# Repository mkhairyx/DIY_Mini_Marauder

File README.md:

# DIY_Mini_Marauder

This is an open source version of [JustCallMeKoko's](github.com/justcallmekoko) marauder mini with better documentation and tutorials on how flash the device after making it. <br>
<br>

The reason I made this repository is becaused I have always wanted to have my own marauder mini but it was unavailble and there was no Schematics to be found for it. <br>
Only thing I was able to find was the PCB and the Case for it. I reverse engineered the PCB to have a useful schematic that anyone can use to make their own PCB and maybe make changes to it. <br>

## The Poster

## The Design
### The PCB

### The Schematics

### The Enclosure Case 
With the device inside:

Without the device inside:

## Assembly
### Step Files
All of the step files can be downloaded [here](./Step_Files/).

### Disassembly video

https://github.com/user-attachments/assets/7e853b93-fa27-431c-8479-e6c7b8179391

## Firmware
### Fzee flasher (Marauder Mini)
- Visit the [FZEE FLASHER](https://fzeeflasher.com/) website
- Make sure your device is connected to your PC
- Click "Connect" <br>

- Select the Programmer chip for your device (which would be CP2104 if you used the schematics/PCB in this repository) <br>

- If you used the schematics/PCB provided in this repository, then you can skip this step. <br>
As soon as you see this screen, hold down the BOOT button on your device as the flasher will automatically reset the device and it will go into the boatloader mode <br>

- Select "ESP32 Marauder Mini Device" <br>

- Select the latest version <br>

- Select "Marauder" as the firmware <br>

- Erase the device first to make sure that it's not affected by any previously installed firmwares <br>

- Click "Program" <br>

- It will take arround 10 seconds to flash the firmware.  <br>
  After those 10 seconds, you should see this screen which indicates that you succesfully flashed the device with the new firmware: <br>

### Bruce (Bruce's Firmware)
- Visit [Bruce's Web Firmware Flasher](https://bruce.computer/flasher) 
- Select whatever release you want (it's recommended to select the latest release)

- Select "Custom Boards"

- Select "Marauder Mini"

- Select "Connect to Device"

- Select the Programmer chip for your device (which would be CP2104 if you used the schematics/PCB in this repository)

- Select "Instal Marauder-Mini"

- Then make sure to have the "Erase device" option enabled then click next

- Confirm the instalation

- If you used the schematics/PCB provided in this repository, then you can skip this step. <br>
As soon as you see this screen, make sure to put your device into the bootloader mode by holding the BOOT button down, pressing the RST button, and then after 2 seconds release the BOOT button.

- It will take around 2 minutes to upload the firmware. <br>
After those 2 minutes, you should see this screen which indicates that you had a succesful instalation:

## Buttons and leds
### The two LEDs
Next to the USB-C port there are 2 LEDs: <br>
- The white one indicates wether the device is powered or not. <br>
- The blue one indicates wether the device is recieved power from the USB-C port or not (which is used to charge the battery).

### The two buttons on the back of the device and their functions
- The Upper button is used to put the ESP32 into the bootloader mode (AKA. the BOOT button). <br>
- The lower button is used to reset the device (AKA. the RST button).<br>

### The side switch
- The side switch is used to power the device ON or OFF.

## BOM
### BOM table (components only)
|Name                            |Value                       |Link                                                                                                                                                                                                                                                                                                                                                                    |Cost (EGP) per one|Cost (USD)|Total Cost (EGP)                           |Total Cost (USD)|Qty of packages|Description          |quantiy per pack|
|--------------------------------|----------------------------|------------------------------------------------------------------------------------------------------------------------------------------------------------------------------------------------------------------------------------------------------------------------------------------------------------------------------------------------------------------------|------------------|----------|-------------------------------------------|----------------|---------------|---------------------|----------------|
|Capacitor                       |100nF                       |https://lampatronics.com/product/smd-multilayer-ceramic-capacitor-0805-2012-104-100nf-50v-1pcs-2                                                                                                                                                                                                                                                                        | EGP 1.00         | $0.02    | EGP 3.00                                  | $0.06          |3              |                     |1               |
|Capacitor                       |4.7uF                       |https://lampatronics.com/product/smd-multilayer-ceramic-capacitor-1206-4-7uf-16v-1pcs                                                                                                                                                                                                                                                                                   | EGP 1.50         | $0.03    | EGP 4.50                                  | $0.09          |3              |                     |1               |
|Capacitor                       |2.2uF                       |https://lampatronics.com/product/smd-multilayer-ceramic-capacitor-0805-2-2uf-50v-1pcs                                                                                                                                                                                                                                                                                   | EGP 1.00         | $0.02    | EGP 1.00                                  | $0.02          |1              |                     |1               |
|SD Card slot                    |TF-115                      |https://lampatronics.com/product/push-push-type-tf-micro-sd-card-socket-adapter-automatic-pcb-connector                                                                                                                                                                                                                                                                 | EGP 8.00         | $0.15    | EGP 8.00                                  | $0.15          |1              |                     |1               |
|Charging LED                    |SZYY0603Y                   |https://lampatronics.com/product/smd-led-0805-blue-10pcs                                                                                                                                                                                                                                                                                                                | EGP 8.00         | $0.15    | EGP 8.00                                  | $0.15          |1              |Charge LED (RED)     |10              |
|Power LED                       |SZYY0603Y                   |https://lampatronics.com/product/smd-led-0805-white-10pcs                                                                                                                                                                                                                                                                                                               | EGP 8.00         | $0.15    | EGP 8.00                                  | $0.15          |1              |Power LED (White)    |10              |
|Schottky Diode                  |MBR120LSF (alt: 1N5819 SS14)|https://uge-one.com/product/smd-schottky-diode-1n5819-ss14-1a-40v-sma-package/                                                                                                                                                                                                                                                                                          | EGP 2.50         | $0.05    | EGP 2.50                                  | $0.05          |1              |Schottky             |1               |
|JST Connector                   |S2B-PH-SM4-TB               |https://uge-one.com/product/jst-connector-male-polarized-xh2-54-2p/                                                                                                                                                                                                                                                                                                     | EGP 1.14         | $0.02    | EGP 1.14                                  | $0.02          |1              |JST connector        |1               |
|BOOT and RESET transistors      |S8050                       |https://lampatronics.com/product/s8050-transistor-40v-0-5a-npn                                                                                                                                                                                                                                                                                                          | EGP 0.50         | $0.01    | EGP 1.00                                  | $0.02          |2              |RST&BOOT transistors |1               |
|Power management and TFT LED PWM|AO3401                      |https://uge-one.com/product/ao3401-sot23-general-purpose-p-channel-mosfet-smd-transistor-sot-23/                                                                                                                                                                                                                                                                        | EGP 3.00         | $0.06    | EGP 6.00                                  | $0.12          |2              |Power manage, TFT LED|1               |
|Resistor                        |5.1k                        |https://uge-one.com/product/smd-chip-resistor-size-0603-5-1k-ohm/                                                                                                                                                                                                                                                                                                       | EGP 0.50         | $0.01    | EGP 1.00                                  | $0.02          |2              |USB-C resistors 5.1k |1               |
|Resistor                        |10K                         |https://lampatronics.com/product/smd-resistor-10kohm-103-0805-10pcs                                                                                                                                                                                                                                                                                                     | EGP 2.00         | $0.04    | EGP 4.00                                  | $0.08          |2              |                     |10              |
|Resistor                        |1K                          |https://lampatronics.com/product/smd-resistor-1kohm-102-0805-10pcs                                                                                                                                                                                                                                                                                                      | EGP 2.00         | $0.04    | EGP 2.00                                  | $0.04          |1              |                     |10              |
|Prog Resistor                   |2K                          |https://lampatronics.com/product/smd-resistor-2kohm-202-0805-10pcs                                                                                                                                                                                                                                                                                                      | EGP 2.00         | $0.04    | EGP 2.00                                  | $0.04          |1              |                     |10              |
|RST and BOOT buttons            |SW_Omron_B3FS               |https://lampatronics.com/product/smd-push-button-3425mm-tactile-tact-micro-switch-momentary-4pin                                                                                                                                                                                                                                                                        | EGP 3.00         | $0.06    | EGP 6.00                                  | $0.12          |2              |                     |1               |
|LDO Enable Switch               |K3-1296S-E1_C128955         |https://uge-one.com/product/horizontal-small-slide-toggle-switch-spdt-3pin-2mm-pin-spacing-sk12d02vg7/                                                                                                                                                                                                                                                                  | EGP 4.00         | $0.08    | EGP 4.00                                  | $0.08          |1              |Power slide switch   |1               |
|directional buttons             |                            |https://lampatronics.com/product/push-button-4pin-long-6x6x13mm                                                                                                                                                                                                                                                                                                         | EGP 1.50         | $0.03    | EGP 7.50                                  | $0.14          |5              |Directional switch   |1               |
|MCU                             |ESP32-WROOM-32              |https://uge-one.com/product/espressif-esp32-wroom-32-dual-core-wi-fi-bluetooth-iot-module/                                                                                                                                                                                                                                                                              | EGP 290.00       | $5.58    | EGP 290.00                                | $5.58          |1              |MCU                  |1               |
|Battery charger                 |MCP73831T-2ACI_OT           |[Long Aliexpress link](https://ar.aliexpress.com/item/32844180448.html?spm=a2g0o.productlist.main.1.3ce63cd6piQzMy&algo_pvid=c4aa9c81-0eb9-4713-ae7a-3ae3d38d7e01&pdp_ext_f=%7B%22order%22%3A%22167%22%2C%22spu_best_type%22%3A%22price%22%2C%22eval%22%3A%221%22%2C%22fromPage%22%3A%22search%22%7D&utparam-url=scene%3Asearch%7Cquery_from%3A%7Cx_object_id%3A32844180448%7C_p_origin_prod%3A)| N/A              | $4.28    | N/A                                       | $4.28          |1              |Battery Charger      |10              |
|Programmer                      |CP2104                      |[Long Aliexpress link](https://ar.aliexpress.com/item/1005012309258723.html?pdp_ext_f=%7B%22sku_id%22%3A%2212000058021215527%22%7D&sourceType=1&spm=a2g0o.wish-manage-home.0.0&gatewayAdapt=glo2ara)                                                                                                                                                                    | N/A              | $1.97    | N/A                                       | $1.97          |1              |USB to TTL chip      |1               |
|LDO Regulator                   |MIC5219-3.3YM5              |[Long Aliexpress link](https://ar.aliexpress.com/item/1005006130724980.html?spm=a2g0o.productlist.main.6.4c73EOI6EOI6w7&algo_pvid=ba305fa5-d1fa-45ea-b339-9e0b52087c6d&pdp_ext_f=%7B%22order%22%3A%2222%22%2C%22eval%22%3A%221%22%2C%22fromPage%22%3A%22search%22%7D&utparam-url=scene%3Asearch%7Cquery_from%3A%7Cx_object_id%3A1005006130724980%7C_p_origin_prod%3A)   | N/A              | $4.23    | N/A                                       | $4.23          |1              |LDO regulator        |10              |
|Display                         |TFT_1.44                    |[Long Aliexpress link](https://ar.aliexpress.com/item/1005001598020071.html?spm=a2g0o.order_list.order_list_main.5.714d1802IvCG36&gatewayAdapt=glo2ara)                                                                                                                                                                                                                 | N/A              | $2.16    | N/A                                       | $2.16          |1              |                     |1               |
|USB-C                           |USB_C_Receptacle_USB2.0_16P |https://www.ram-e-shop.com/shop/usb9-c-type-pcb-usb-connector-on-pcb-c-type-type-female-16-pin-sku-usb9-8125                                                                                                                                                                                                                                                            | EGP 5.00         | $0.10    | EGP 5.00                                  | $0.10          |1              |                     |1               |
|Battery                         |700 mah                     |https://lampatronics.com/product/battery-polymer-3-7v-700mah-li-ion-single-cell-35x20x5mm-502035                                                                                                                                                                                                                                                                        | EGP 135.00       | $2.60    | EGP 135.00                                | $2.60          |1              |                     |1               |
|M5 Screws                       |M5*16mm                     |https://store.fut-electronics.com/products/screw-m5x16mm-hexagonal-head?_pos=15&_sid=376b1bf88&_ss=r                                                                                                                                                                                                                                                                    | EGP 2.00         | $0.04    | EGP 2.00                                  | $0.04          |1              |                     |1               |
|                                |                            |                                                                                                                                                                                                                                                                                                                                                                        |                  |          |                                           |                |               |                     |                |
|                                |                            |                                                                                                                                                                                                                                                                                                                                                                        |                  |          | EGP 501.64                                | $22.29         |               |                     |                |
|                                |                            |                                                                                                                                                                                                                                                                                                                                                                        |                  |          | (Stuff from aliexpress not included here) |                |               |                     |                |

### Orders from different manufacturers
#### In Egypt
[Nori](norisolutions.com) (PCB only): $19.09 <br>

<br>

 [Metanoia](metanoia-eg.com) (Case only): $5.96 <br>
 
<br>

#### Out of Egypt
[JLCPCB](https://jlcpcb.com/) (both PCB and Case): $31.15 <br>

<br>
<br>
<br>

<h1 align="center"> DISCLAIMER </h1>

<h4 align="center">Please note that the use of this tool is entirely at your own risk. It is intended strictly for educational purposes and should not be used for any illegal or unethical activities. Jamming is illegal and can get you in big trouble!</h4>
<h4 align="center">I'm not responsible for your actions! </h4>

<br>

> The firmware is designed by [JustCallMeKoko](github.com/justcallmekoko). <br>
The PCB that was reverse engineered for the making of [DIY Mini Marauder](https://github.com/mkhairyx/DIY_Mini_Marauder) is designed by [JustCallMeKoko](https://github.com/justcallmekoko).<br>
This repo and all of it's contents were Designed by [@mkhairyx](https://github.com/mkhairyx).<br>
Supported by [Fallout](https://fallout.hackclub.com/) and [Hack Club](https://hackclub.com).<br>

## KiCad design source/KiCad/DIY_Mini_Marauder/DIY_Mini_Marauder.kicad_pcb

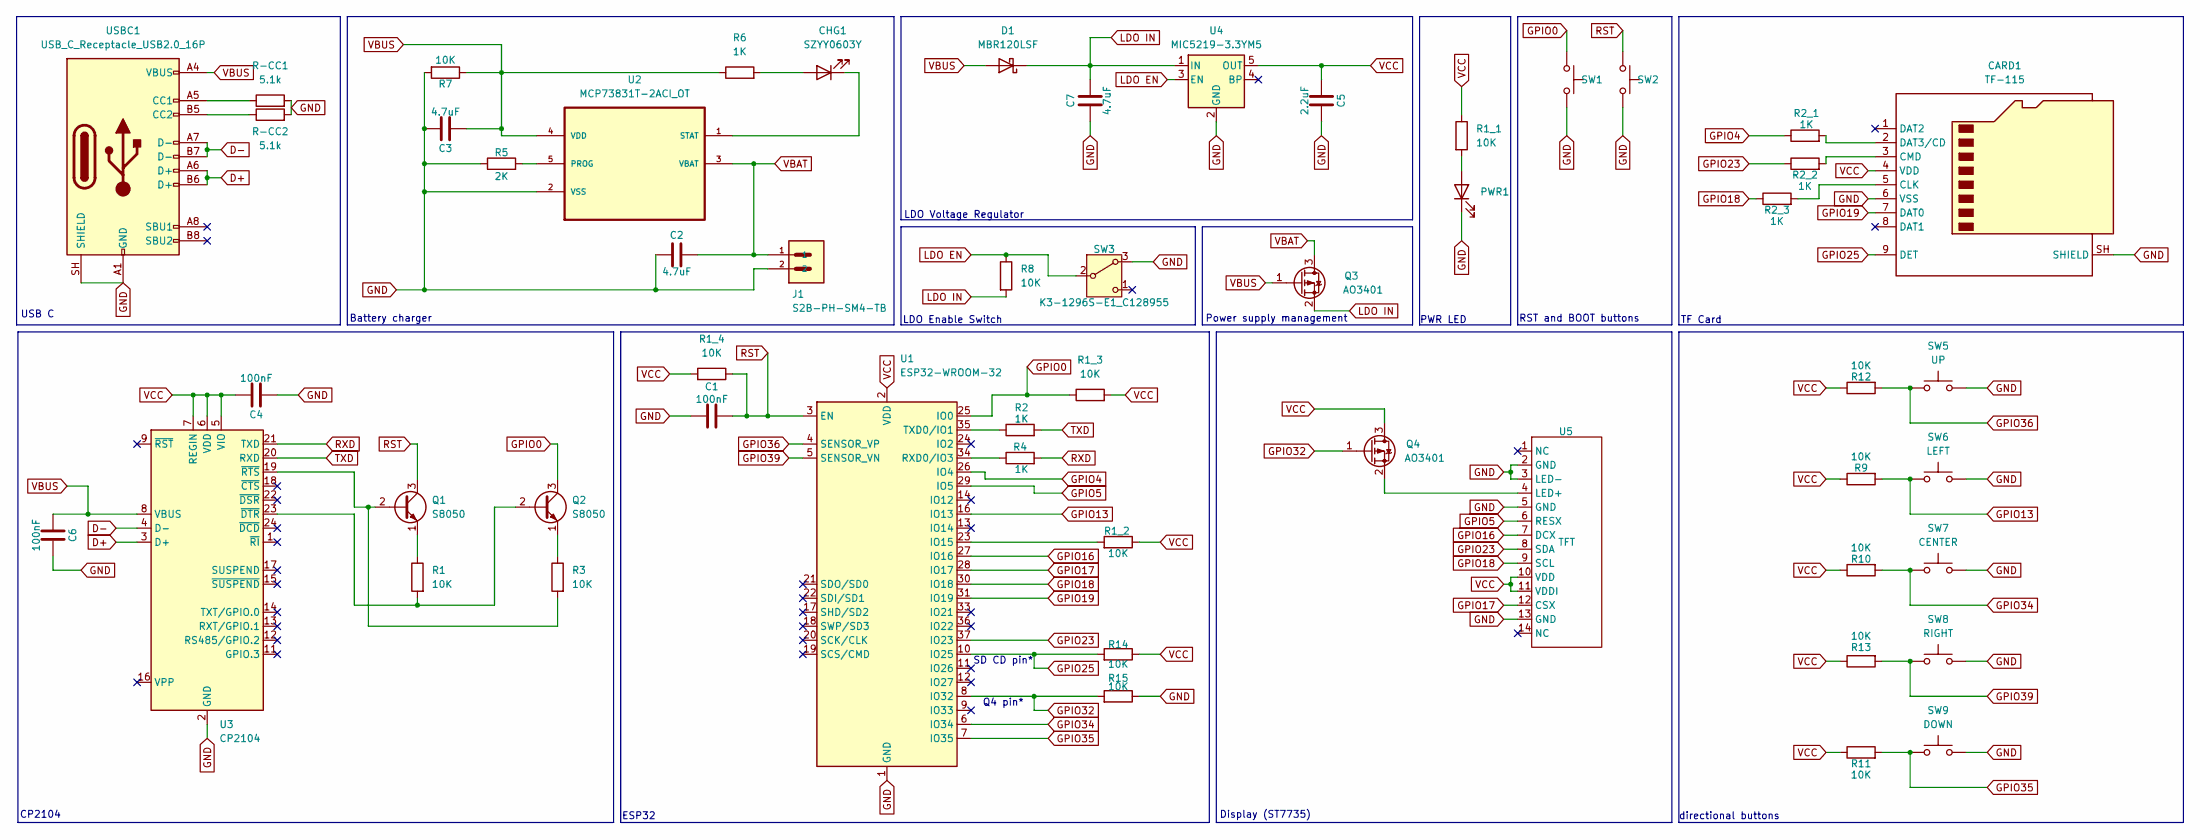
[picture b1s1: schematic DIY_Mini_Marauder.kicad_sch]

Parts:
C1, C4, C6: 100nF; C_0805_2012Metric_Pad1.18x1.45mm_HandSolder
C2, C3, C7: 4.7uF; C_1206_3216Metric_Pad1.33x1.80mm_HandSolder
C5: 2.2uF; C_0805_2012Metric_Pad1.18x1.45mm_HandSolder
CARD1: TF-115
CHG1: SZYY0603Y; LED_0805_2012Metric_Pad1.15x1.40mm_HandSolder
D1: MBR120LSF; D_SMA_Handsoldering
J1: S2B-PH-SM4-TB; JST_EH_B2B-EH-A_1x02_P2.50mm_Vertical
PWR1: SZYY0603Y; LED_0805_2012Metric_Pad1.15x1.40mm_HandSolder
Q1, Q2: S8050; TO-92
Q3, Q4: AO3401; SOT-23
R1, R1_1, R1_2, R1_3, R1_4, R3, R7, R8, R9, R10, R11, R12, R13, R14, R15: 10K; R_0805_2012Metric_Pad1.20x1.40mm_HandSolder
R2, R2_1, R2_2, R2_3, R4, R6: 1K; R_0805_2012Metric_Pad1.20x1.40mm_HandSolder
R5: 2K; R_0805_2012Metric_Pad1.20x1.40mm_HandSolder
R-CC1, R-CC2: 5.1k; R_0603_1608Metric_Pad0.98x0.95mm_HandSolder
SW1, SW2: SW_Omron_B3FS; SW_SPST_PTS810
SW3: K3-1296S-E1_C128955; SW_Slide_SPDT_Angled_CK_OS102011MA1Q
SW5: UP; SW_PUSH_6mm_H13mm
SW6: LEFT; SW_PUSH_6mm_H13mm
SW7: CENTER; SW_PUSH_6mm_H13mm
SW8: RIGHT; SW_PUSH_6mm_H13mm
SW9: DOWN; SW_PUSH_6mm_H13mm
U1: ESP32-WROOM-32
U2: MCP73831T-2ACI_OT; SOT-23-5_HandSoldering; MPN MCP73831T-2ACI/OT
U3: CP2104; QFN-24-1EP_4x4mm_P0.5mm_EP2.6x2.6mm
U4: MIC5219-3.3YM5; SOT-23-5_HandSoldering
U5: TFT; ST7735_TFT_14P
USBC1: USB_C_Receptacle_USB2.0_16P; USB_C_Receptacle_GCT_USB4105-xx-A_16P_TopMnt_Horizontal

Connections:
D+: U3.3 (D+), USBC1.A6 (D+), USBC1.B6 (D+)
D-: U3.4 (D-), USBC1.A7 (D-), USBC1.B7 (D-)
GND: C1.1, C2.1, C3.2, C4.1, C5.2, C6.2, C7.1, CARD1.6 (VSS), CARD1.SH (SHIELD), J1.2, PWR1.1 (K), R5.1, R7.2, R15.1, R-CC1.2, R-CC2.2, SW1.1, SW2.1, SW3.3 (A), SW5.2, SW6.2, SW7.2, SW8.2, SW9.2, U1.1 (GND), U1.15 (GND), U1.38 (GND), U1.39 (GND), U2.2 (VSS), U3.2 (GND), U3.25 (GND), U4.2 (GND), U5.2 (GND), U5.3 (LED-), U5.5 (GND), U5.13 (GND), USBC1.A1 (GND), USBC1.A12 (GND), USBC1.B1 (GND), USBC1.B12 (GND), USBC1.SH (SHIELD)
GPIO0: Q2.3 (C), R1_3.1, SW1.2, U1.25 (IO0)
GPIO4: R2_1.1, U1.26 (IO4)
GPIO5: U1.29 (IO5), U5.6 (RESX)
GPIO13: R9.2, SW6.1, U1.16 (IO13)
GPIO16: U1.27 (IO16), U5.7 (DCX)
GPIO17: U1.28 (IO17), U5.12 (CSX)
GPIO18: R2_3.1, U1.30 (IO18), U5.9 (SCL)
GPIO19: CARD1.7 (DAT0), U1.31 (IO19)
GPIO23: R2_2.1, U1.37 (IO23), U5.8 (SDA)
GPIO25: CARD1.9 (DET), R14.2, U1.10 (IO25)
GPIO32: Q4.1 (G), R15.2, U1.8 (IO32)
GPIO34: R10.2, SW7.1, U1.6 (IO34)
GPIO35: R11.2, SW9.1, U1.7 (IO35)
GPIO36: R12.2, SW5.1, U1.4 (SENSOR_VP)
GPIO39: R13.2, SW8.1, U1.5 (SENSOR_VN)
LDO EN: R8.1, SW3.2 (B), U4.3 (EN)
LDO IN: C7.2, D1.1 (K), Q3.2 (S), R8.2, U4.1 (IN)
unnamed: CARD1.5 (CLK), R2_3.2
unnamed: CARD1.3 (CMD), R2_2.2
unnamed: CARD1.2 (DAT3/CD), R2_1.2
unnamed: CHG1.2 (A), R6.2
unnamed: CHG1.1 (K), U2.1 (STAT)
unnamed: PWR1.2 (A), R1_1.2
unnamed: Q1.2 (B), R3.2, U3.19 (~RTS)
unnamed: Q1.1 (E), R1.1
unnamed: Q2.2 (B), R1.2, U3.23 (~DTR)
unnamed: Q2.1 (E), R3.1
unnamed: Q4.2 (S), U5.4 (LED+)
unnamed: R1_2.2, U1.23 (IO15)
unnamed: R4.1, U1.34 (RXD0/IO3)
unnamed: R2.1, U1.35 (TXD0/IO1)
unnamed: R5.2, U2.5 (PROG)
unnamed: R-CC1.1, USBC1.A5 (CC1)
unnamed: R-CC2.1, USBC1.B5 (CC2)
RST: C1.2, Q1.3 (C), R1_4.1, SW2.2, U1.3 (EN)
RXD: R4.2, U3.21 (TXD)
TXD: R2.2, U3.20 (RXD)
VBAT: C2.2, J1.1, Q3.3 (D), U2.3 (VBAT)
VBUS: C3.1, C6.1, D1.2 (A), Q3.1 (G), R6.1, R7.1, U2.4 (VDD), U3.8 (VBUS), USBC1.A4 (VBUS), USBC1.A9 (VBUS), USBC1.B4 (VBUS), USBC1.B9 (VBUS)
VCC: C4.2, C5.1, CARD1.4 (VDD), Q4.3 (D), R1_1.1, R1_2.1, R1_3.2, R1_4.2, R9.1, R10.1, R11.1, R12.1, R13.1, R14.1, U1.2 (VDD), U3.5 (VIO), U3.6 (VDD), U3.7 (REGIN), U4.5 (OUT), U5.10 (VDD), U5.11 (VDDI)

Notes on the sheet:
directional buttons
LDO Enable Switch
SD CD pin*
Power supply management
LDO Voltage Regulator
Q4 pin*
USB C
Battery charger
RST and BOOT buttons
TF Card
PWR LED
ESP32
CP2104
Display (ST7735)

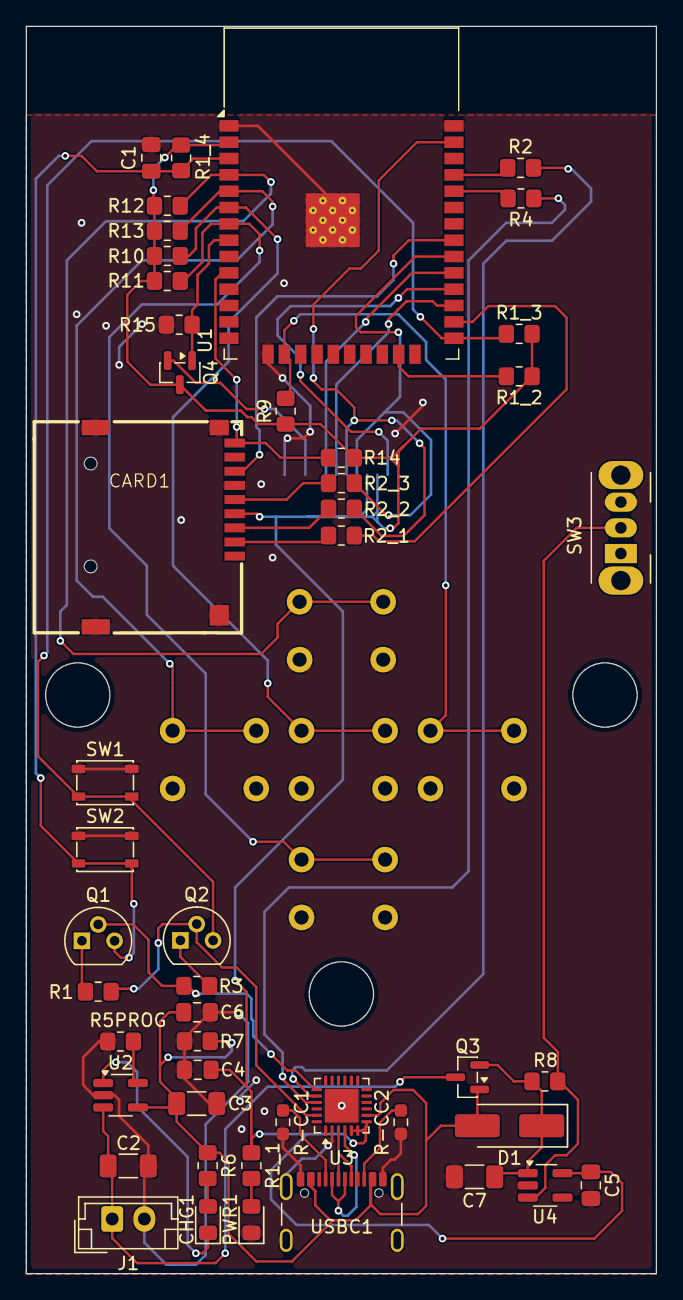
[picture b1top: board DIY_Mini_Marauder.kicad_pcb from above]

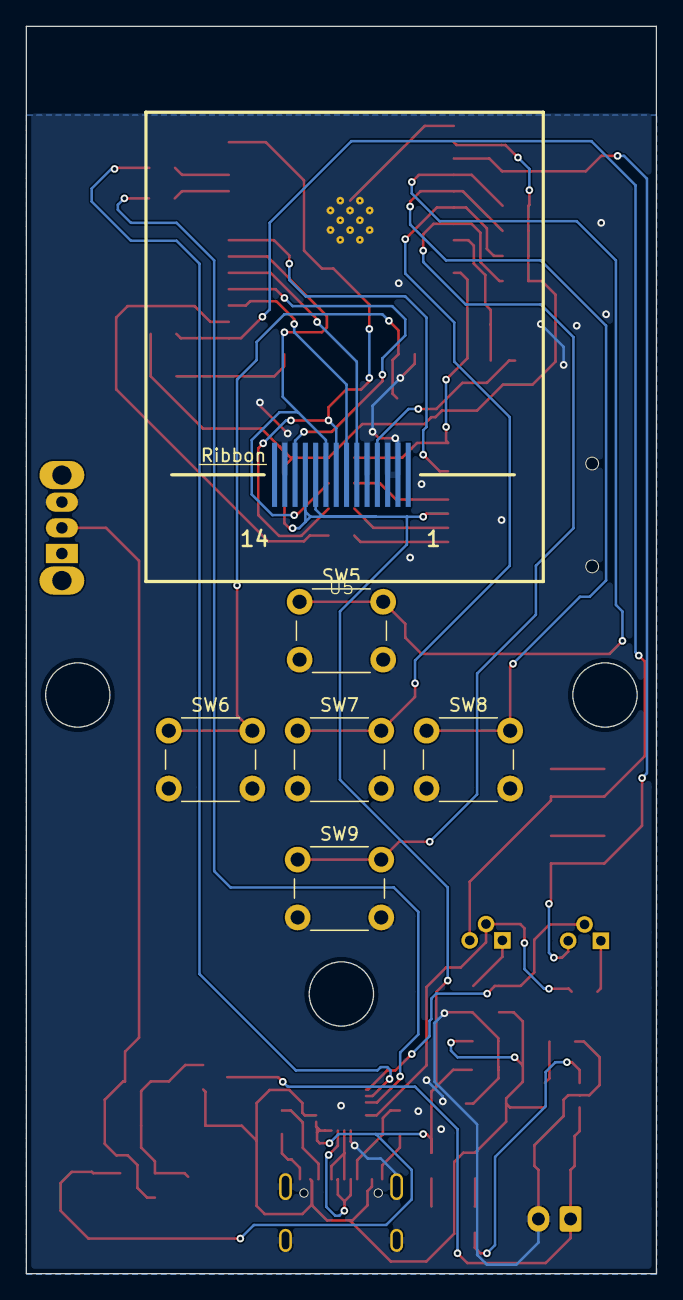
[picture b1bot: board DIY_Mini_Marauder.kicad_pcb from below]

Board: 2 copper layers, 49.0 x 97.0 mm, 54 parts (6 on the bottom side), 43 nets.

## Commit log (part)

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2026-06-12 Uploading the files to git
2026-06-12 Fix typo in README.md link reference
2026-06-12 Added BOM
2026-06-13 uploading files from other device
2026-06-13 Done most of the readme
2026-06-13 finished most of the readme
2026-06-13 Renamed picture
2026-06-14 Revise README for improved documentation and tutorials
    Updated README to include better documentation and tutorials for flashing the device. Added links and images for assembly and firmware installation.
2026-06-14 Revise README for clarity and structure
    Updated README to improve documentation and formatting.
2026-06-15 Added files for rendering and a rendered picutre
2026-06-15 edited blender files
2026-06-16 Rendered image
    Screen brighter
2026-06-16 Saved changes in blender
    Made the screen brighter
2026-06-16 Edited render and added a new pic
    Added a sun light
2026-06-16 Added poster stuff
    zine pdf, png, psd, excalidraw.
2026-06-16 Update README with poster and cost changes
    Added a poster image and updated the cost for the case from Metanoia.
2026-06-16 renamed folders
2026-06-16 Enhance README with personal motivation and clarity
    Added a personal motivation for creating the repository and improved clarity in the introduction.
2026-06-20 Changed things with the zine poster.
2026-06-20 Fix formatting and update README content
2026-06-20 Revise README for clarity and additional information
    Updated README with project details, assembly instructions, firmware flashing guide, BOM, and manufacturer information.
